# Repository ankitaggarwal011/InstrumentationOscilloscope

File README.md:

# Instrumentation Oscilloscope

A portable, low-cost oscilloscope for laboratory and educational usage

## Abstract

Oscilloscopes are the devices used to observe varying signal voltages. Originally, the oscilloscopes are considered as costly, bulky and standalone devices. The project aims at building a low cost, low power, hand-held and portable oscilloscope with the basic utilities for efficient laboratory use. The device consists primarily of three parts, viz. signal conditioning, power management and micro-controller unit. The project has sampling as the basic technical basis, and the other circuits are employed to ensure minimal errors and maximal efficiency. The micro-controller unit is integrated with an LCD display which displays the signal along with its frequency and amplitude values.

**Please read the Technical Report included with each implementation for detailed information.**

## Motivation

The project was a top submission in multiple national design contests.
- Top 100 out of 1800 national proposals in [Texas Instruments Analog Design Contest 2014](http://youtu.be/NTonO6jmq0U). Implementation on TI MSP430 micro-controller.
- Top 50 out of 1000 national proposals in [Freescale Design Contest 2014](http://youtu.be/67Osx63GCeo). Implementation on FRDM-KL25Z micro-controller.

## Usage

The following files are included with each implementation:
- Schematic and PCB Layout
- Technical Report
- Source Code in in Embedded C/Arduino

#### Notes:
- For TI MSP430 implementation, the code was compiled and burned into micro-controller using Energia IDE.
- For FRDM-KL25Z implementation, the code was compiled and burned into micro-controller using mbed online platform.

## Contribute

Want to work on the project? Any kind of contribution is welcome!

Follow these steps:
- Fork the project.
- Create a new branch.
- Make your changes and write tests when practical.
- Commit your changes to the new branch.
- Send a pull request.

## License

[MIT License](https://github.com/ankitaggarwal011/InstrumentationOscilloscope/blob/master/LICENSE)

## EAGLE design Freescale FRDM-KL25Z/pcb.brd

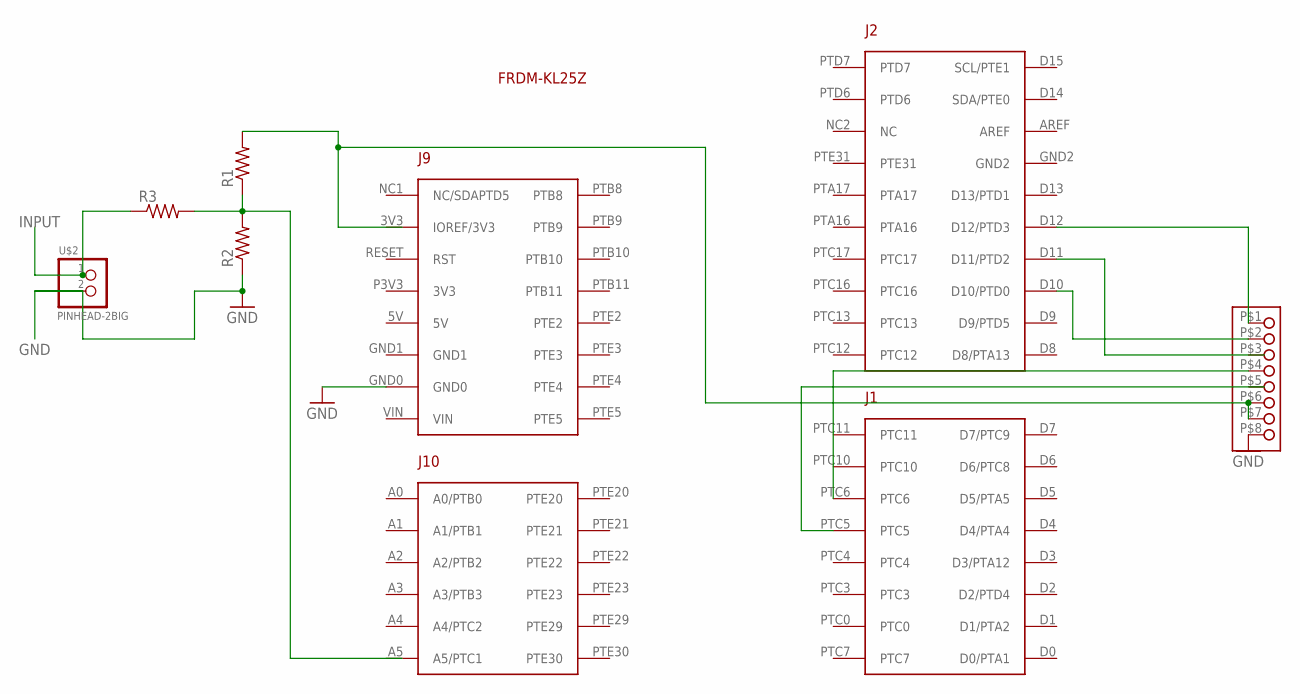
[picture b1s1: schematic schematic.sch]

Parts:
FRDM1: FRDM-KL25ZARDUINO; FRDM-KL25Z
R1, R2, R3: R-US_0204/5; 0204/5
U$1: PINHEAD-8; PTH-8-1MM
U$2: PINHEAD-2BIG; BIGPIN-2

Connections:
GND: FRDM1.GND0, R2.1, U$1.P$8, U$2.P$2 (2)
INPUT: R3.1, U$2.P$1 (1)
unnamed: R1.2, U$1.P$6, U$1.P$7
unnamed: FRDM1.D12 (D12/PTD3), U$1.P$1
unnamed: R1.1, R2.2, R3.2
unnamed: FRDM1.D10 (D10/PTD0), U$1.P$2
unnamed: FRDM1.PTC6, U$1.P$4

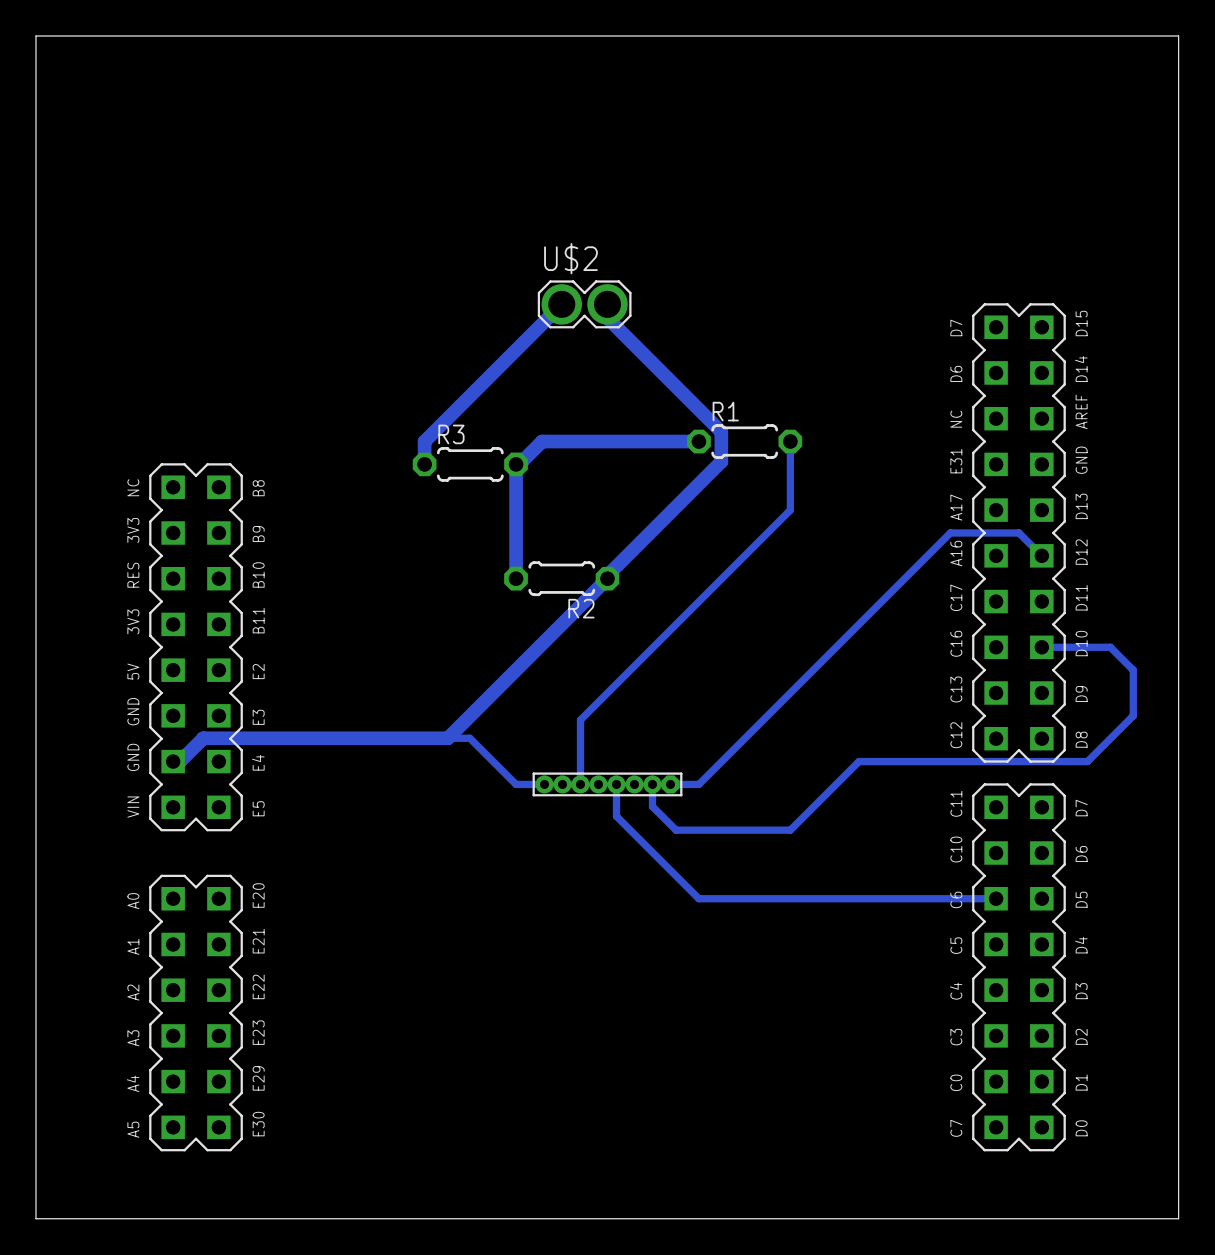
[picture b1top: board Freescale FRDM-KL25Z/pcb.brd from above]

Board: 2 copper layers, 63.5 x 65.7 mm, 6 parts (0 on the bottom side), 7 nets.

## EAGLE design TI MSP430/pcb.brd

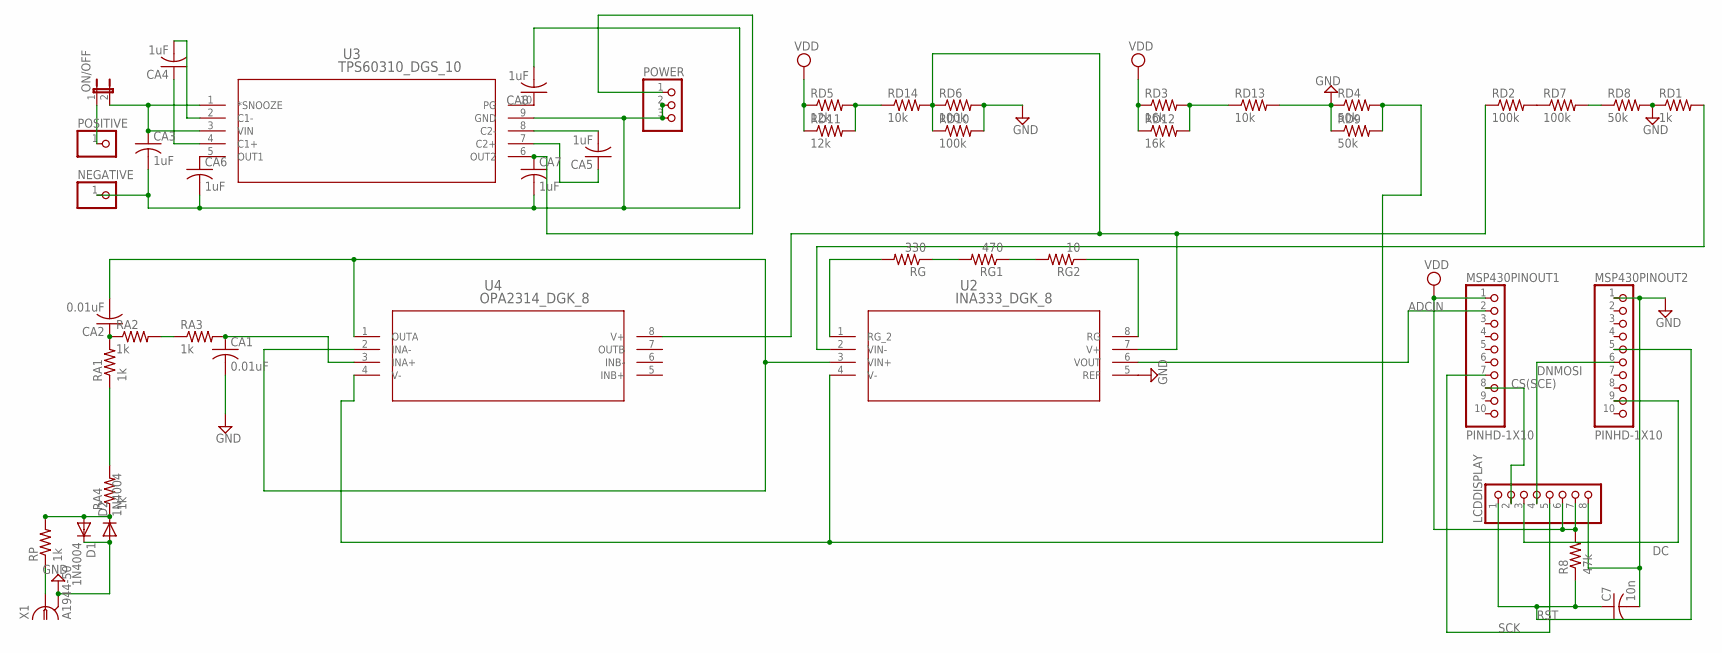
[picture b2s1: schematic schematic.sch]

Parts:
C7: 10n; C025-024X044
CA1, CA2: 0.01uF; C025-024X044
CA3, CA4, CA5, CA6, CA7, CA8: 1uF; C025-024X044
D1, D2: 1N4004; DO41-10
LCDDISPLAY: PINHD-1X8BIG; 1X08-BIG
MSP430PINOUT1, MSP430PINOUT2: PINHD-1X10; 1X10-BIG
NEGATIVE: PINHD-1X1; 1X01
ON/OFF: JP1E; JP1
POSITIVE: PINHD-1X1; 1X01
POWER: PINHD-1X3; 1X03
R8: 47k; 0204/7
RA1, RA2, RA3, RA4: 1k; 0204/7
RD1: 1k; 0204/7
RD2, RD6, RD7, RD10: 100k; 0204/7
RD3, RD12: 16k; 0204/7
RD4, RD8, RD9: 50k; 0204/7
RD5, RD11: 12k; 0204/7
RD13, RD14: 10k; 0204/7
RG: 330; 0204/7
RG1: 470; 0204/7
RG2: 10; 0204/7
RP: 1k; 0204/7
U2: INA333_DGK_8; DGK8
U3: TPS60310_DGS_10; DGS10
U4: OPA2314_DGK_8; DGK8
X1: A1944-50; A1944

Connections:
ADCIN: MSP430PINOUT1.2, U2.6 (VOUT)
CS(SCE): LCDDISPLAY.2, MSP430PINOUT1.8
DC: LCDDISPLAY.3, MSP430PINOUT2.9
DNMOSI: LCDDISPLAY.4, MSP430PINOUT2.6
GND: C7.2, CA1.2, D1.C, D2.A, LCDDISPLAY.8, MSP430PINOUT2.1, RD1.1, RD4.1, RD6.2, RD8.2, RD9.1, RD10.2, RD13.2, U2.5 (REF), X1.2 (GND), X1.3 (GND), X1.4 (GND), X1.5 (GND)
unnamed: CA3.1, ON/OFF.2, U3.1 (*SNOOZE), U3.3 (VIN)
unnamed: RG.1, RG1.2
unnamed: RG1.1, RG2.2
unnamed: CA2.2, U2.3 (VIN+), U4.1 (OUTA), U4.2 (INA-)
unnamed: D1.A, D2.C, RA4.1, RP.2
unnamed: CA6.1, U3.5 (OUT1)
unnamed: RP.1, X1.1
unnamed: CA2.1, RA1.2, RA2.1
unnamed: RG2.1, U2.8 (RG)
unnamed: CA3.2, CA6.2, CA7.2, CA8.2, NEGATIVE.1, POWER.2, POWER.3, U3.9 (GND)
unnamed: CA4.1, U3.4 (C1+)
unnamed: CA4.2, U3.2 (C1-)
unnamed: RA1.1, RA4.2
unnamed: CA5.1, U3.7 (C2+)
unnamed: CA5.2, U3.8 (C2-)
unnamed: ON/OFF.1, POSITIVE.1
unnamed: RA2.2, RA3.1
unnamed: CA1.1, RA3.2, U4.3 (INA+)
unnamed: CA7.1, POWER.1, U3.6 (OUT2)
unnamed: CA8.1, U3.10 (PG)
unnamed: RG.2, U2.1 (RG_2)
unnamed: RD2.2, RD7.1
unnamed: RD7.2, RD8.1
unnamed: RD5.2, RD11.2, RD14.1
unnamed: RD3.2, RD12.2, RD13.1
RST: C7.1, LCDDISPLAY.1, MSP430PINOUT2.5, R8.1
SCK: LCDDISPLAY.5, MSP430PINOUT1.7
VD: RD2.1, RD6.1, RD10.1, RD14.2, U2.7 (V+), U4.8 (V+)
VDD: LCDDISPLAY.6, LCDDISPLAY.7, MSP430PINOUT1.1, R8.2, RD3.1, RD5.1, RD11.1, RD12.1
VND: RD4.2, RD9.2, U2.4 (V-), U4.4 (V-)
VZ: RD1.2, U2.2 (VIN-)

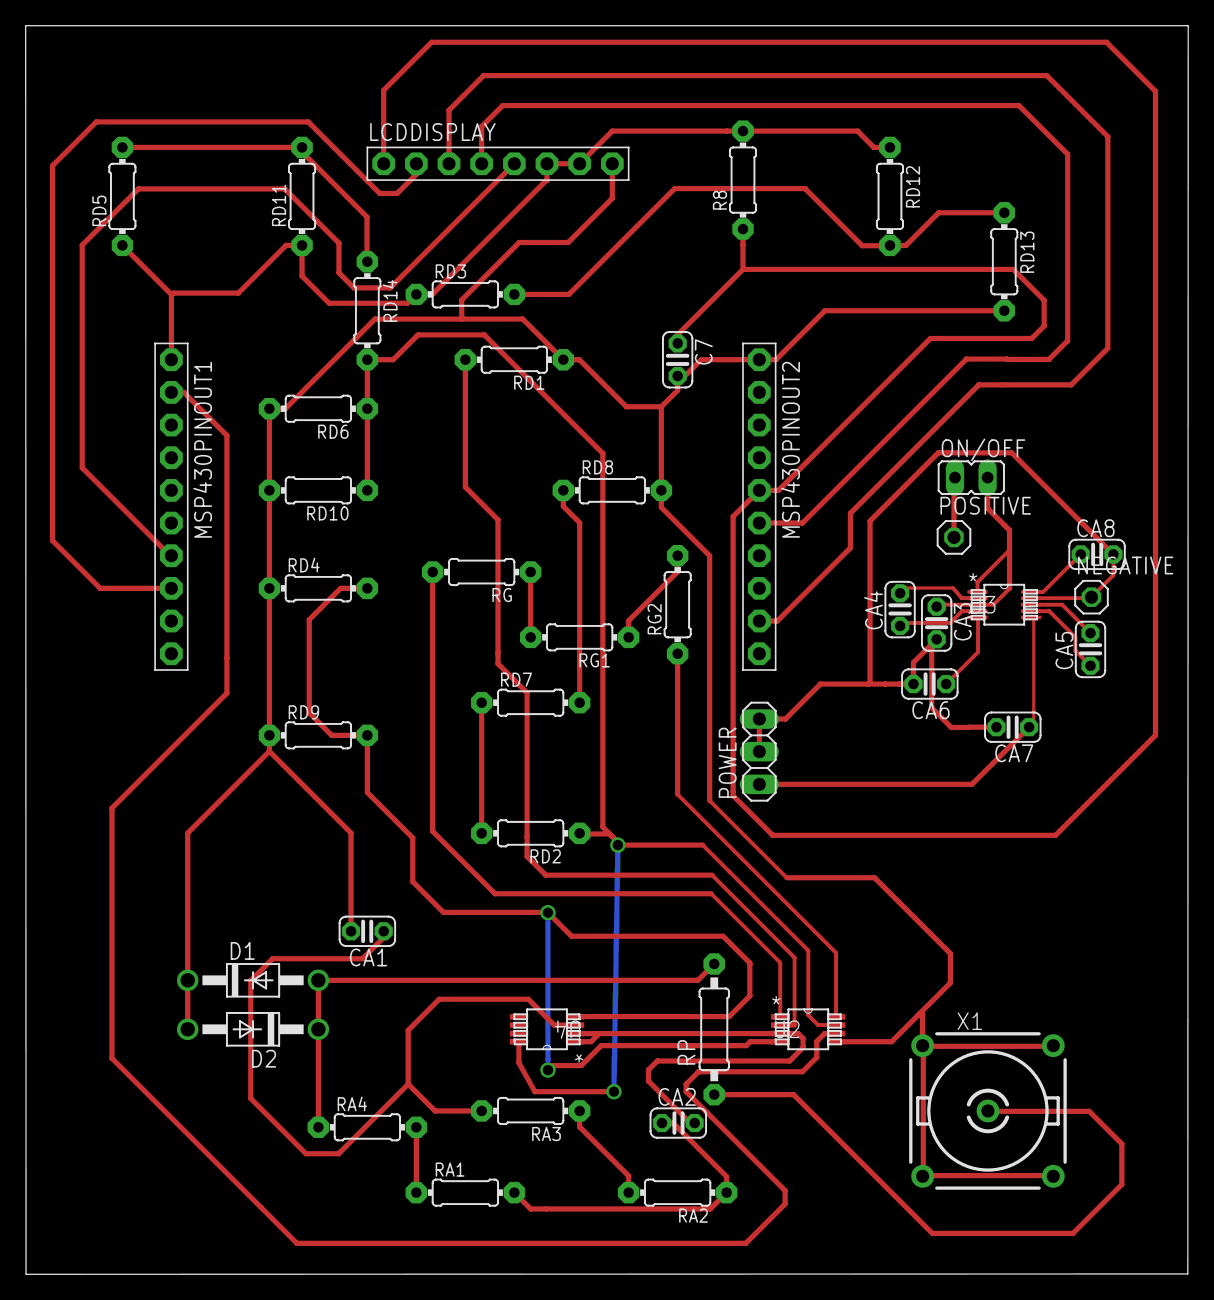
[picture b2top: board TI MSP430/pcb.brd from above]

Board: 2 copper layers, 90.4 x 97.1 mm, 45 parts (0 on the bottom side), 36 nets.

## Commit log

2016-09-30 Updated project.
    Added project content.
    Updated README.
2016-09-30 Updated README.
2016-10-01 Updated structure.

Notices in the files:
parts and their libraries:
SparkFun-Aesthetics: Licensing: Creative Commons ShareAlike 4.0 International - https://creativecommons.org/licenses/by-sa/4.0
